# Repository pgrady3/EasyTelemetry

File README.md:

# EasyTelemetry

A simple telemetry board designed to measure many useful things on an Eco-Marathon car. This board will log quantities to an SD card for later analysis, in addition to providing useful information to the driver on an LCD. This design is hopefully easy to extend.

## Features
* 15v-60v operation
* Based on Teensy 3.2 microcontroller
* Uses INA226 for measuring voltage and low-side current
* Measures vehicle speed using hall gear-tooth sensor
* Measures vehicle position using cheap Chinese Ublox NEO-6M GPS modules
* Integrates instataneous power into total energy (joules) consumed
* Compatible with cheap Chinese 20x4 displays with I2C "LCD backpack"
* Uses TE VAL-U-LOK connectors

## Output File

The software creates log files in the following format

```
39.542 2.804 110.87 5.53 294087.16 5380.27 1407101 4.6546335 114.4687347
39.511 3.111 122.93 5.51 294099.44 5380.78 1407201 4.6546288 114.4687347
39.437 3.854 151.98 5.49 294114.66 5381.30 1407301 4.6546235 114.4687347
39.437 3.854 151.98 5.48 294129.84 5381.82 1407401 4.6546183 114.4687347
39.092 7.068 276.28 5.48 294157.47 5382.34 1407501 4.6546135 114.4687347
39.020 7.721 301.29 5.49 294187.59 5382.85 1407601 4.6546082 114.4687347
```

corresponding to
```
voltage(V) current(A) power(w) velocity(m/s) energy(J) distance(m) elapsed time(ms) latitude(DD.dddd) longitude(DD.dddd)
```

## Schematic

## Board

## Software Used

* PCB layout: [Eagle](https://www.autodesk.com/products/eagle/free-download)
* Compiler: [Arduino](https://www.arduino.cc/) with [PJRC Teensyduino add-on](https://www.pjrc.com/teensy/td_download.html)

## Assembly

This respository includes Gerber files which can be directly submitted to PCB manufacturers. We recommend Chinese manufacturers such as [AllPCB](https://www.allpcb.com/) or [JLCPCB](https://jlcpcb.com/). The repository also includes a Bill of Materials (BOM) with Digikey part numbers to order from.

Assembly is straightforward. However, it is recommended to cut the VIN-VUSB trace on the [underside of the Teensy](https://www.pjrc.com/teensy/card7b_rev1.pdf). Cutting the trace means that the Teensy can no longer be powered over USB. This is a safety procaution to prevent the controller feeding power backwards into your computer's USB port. 

## Contact Us

This controller was designed by Patrick Grady from Duke Electric Vehicles. If you need help or clarification, please [send us a message on our website.](http://www.duke-ev.org/dev-contact-us)

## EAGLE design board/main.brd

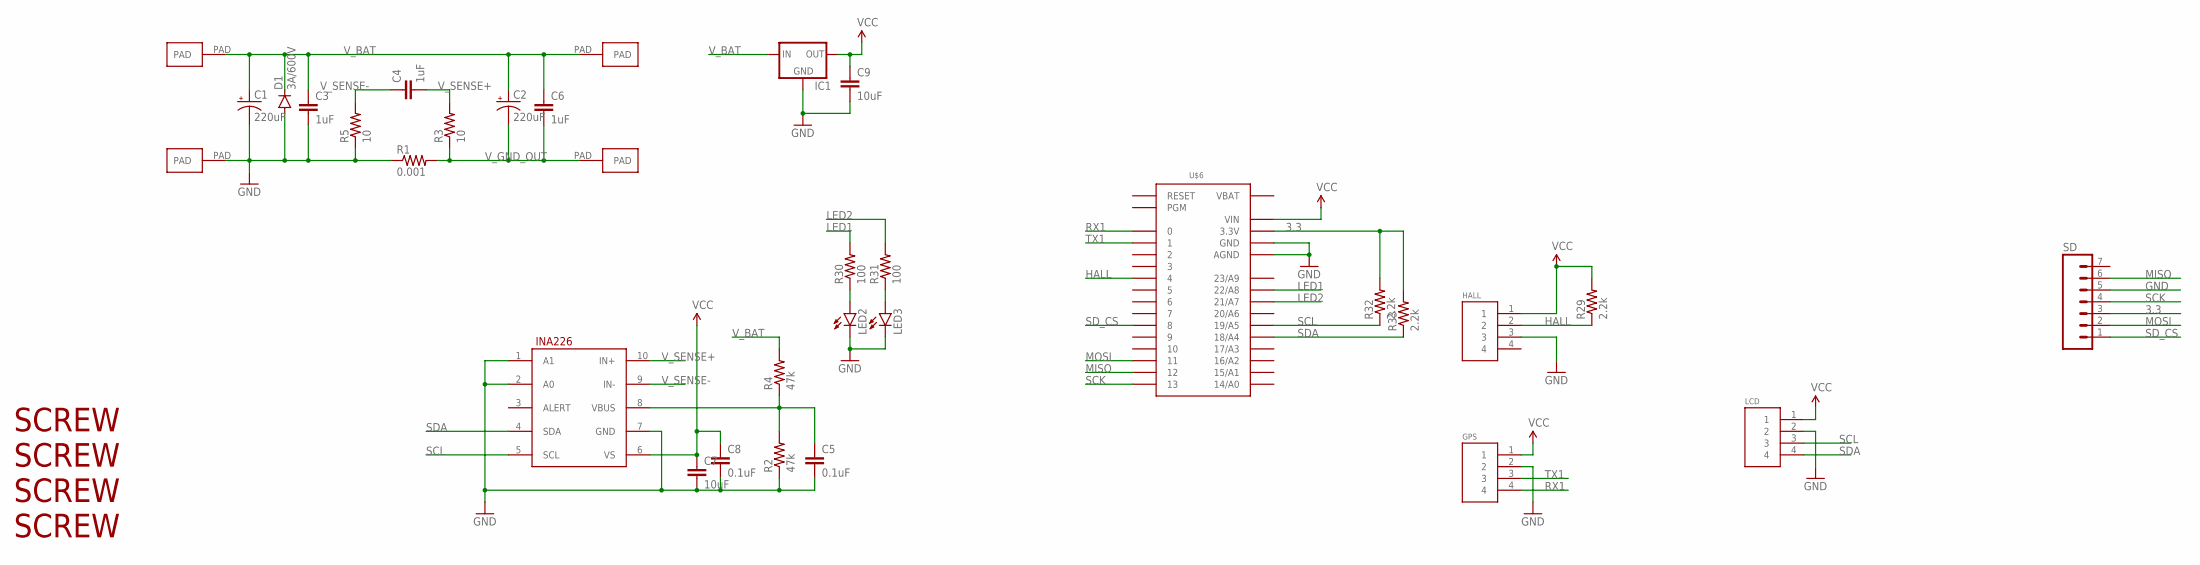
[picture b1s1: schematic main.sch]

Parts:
C1, C2: 220uF; CPOL-RADIAL-1000UF-25V
C3, C4, C6: 1uF; 1206
C5, C8: 0.1uF; 0603-CAP
C7, C9: 10uF; 0805
D1: 3A/600V; SMC
GPS: GPS; 4PINVALULOK
HALL: HEADER4VALULOK; 4PINVALULOK
IC1: V_REG_78XXSINK; TO220-IGO
LCD: GPS; 4PINVALULOK
LED2, LED3: LED1206; LED-1206
R1: 0.001; R2512
R2, R4: 47k; 0603-RES
R3, R5: 10; 0603-RES
R29, R32, R33: 2.2k; 0603-RES
R30, R31: 100; 0603-RES
SD: M07; 1X07
U$1: INA226; PSOP-10
U$2, U$3, U$4, U$5: PAD
U$6: TEENSY_3.0_BASIC
U$13, U$14, U$15, U$16: SCREW; M3HOLE

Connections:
3.3: R32.2, R33.2, SD.3, U$6.3.3V, U$6.3.3V1 (3.3V)
GND: C1.-, C3.2, C5.2, C7.2, C8.2, C9.2, D1.A, GPS.2, HALL.3, IC1.GND, LCD.2, LED2.C, LED3.C, R1.1, R2.1, R5.1, SD.5, U$1.1 (A1), U$1.2 (A0), U$1.7 (GND), U$3.PAD, U$6.AGND, U$6.GND, U$6.GND1 (GND)
HALL: HALL.2, R29.1, U$6.4
LED1: R30.2, U$6.22/A8
LED2: R31.2, U$6.21/A7
MISO: SD.6, U$6.12
MOSI: SD.2, U$6.11
unnamed: C5.1, R2.2, R4.1, U$1.8 (VBUS)
unnamed: LED2.A, R30.1
unnamed: LED3.A, R31.1
RX1: GPS.4, U$6.0
SCK: SD.4, U$6.13
SCL: LCD.3, R32.1, U$1.5 (SCL), U$6.19/A5
SDA: LCD.4, R33.1, U$1.4 (SDA), U$6.18/A4
SD_CS: SD.1, U$6.8
TX1: GPS.3, U$6.1
VBAT: U$6.VBAT
VCC: C7.1, C8.1, C9.1, GPS.1, HALL.1, IC1.OUT, LCD.1, R29.2, U$1.6 (VS), U$6.VIN
V_BAT: C1.+, C2.+, C3.1, C6.1, D1.C, IC1.IN, R4.2, U$2.PAD, U$4.PAD
V_GND_OUT: C2.-, C6.2, R1.2, R3.1, U$5.PAD
V_SENSE+: C4.2, R3.2, U$1.10 (IN+)
V_SENSE-: C4.1, R5.2, U$1.9 (IN-)

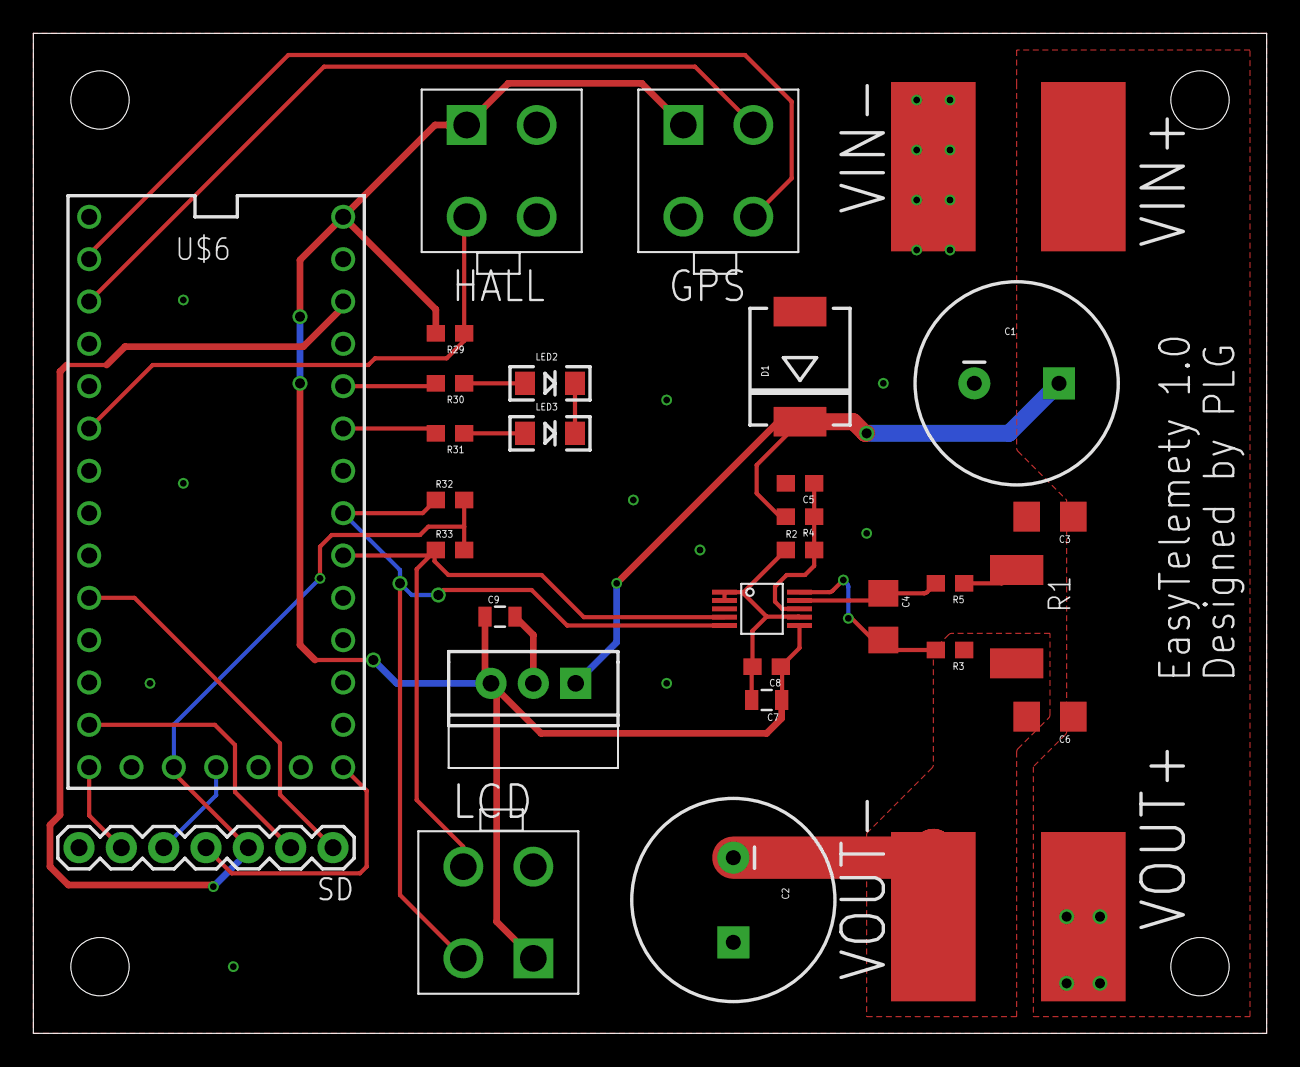
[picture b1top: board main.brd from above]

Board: 2 copper layers, 74.0 x 60.0 mm, 37 parts (0 on the bottom side), 21 nets.

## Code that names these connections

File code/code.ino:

#include <i2c_t3.h>
#include <SD.h>
#include "Adafruit_GPS.h"
#include "LiquidCrystal_I2C.h"
#include "INA.h"

#define LED1 21
#define LED2 22

#define HALL 4
#define SD_CS 8

#define WHEEL_CIRC 1.552
#define WHEEL_TICKS 9
#define TICK_DIST (WHEEL_CIRC / WHEEL_TICKS)

#define TARGET_CURRENT 5

volatile uint32_t tickTimes[WHEEL_TICKS];
volatile uint32_t tickPos;

volatile uint32_t loopTime = 0;
volatile uint32_t lastHallPulse = 0;
volatile uint32_t lastInaMeasurement = 0;
volatile uint32_t countIntervals = 0;
volatile int32_t avgdT = 1000000;
volatile uint32_t distTicks = 0;

double energyUsed = 0.0;
double distance = 0.0;
double currentSpeed = 0.0;
double currentRPM = 0.0;
double InaVoltage = 0.0;
double InaCurrent = 0.0;
double InaPower = 0;
double batteryVoltage = 0.0;
double effScore = 0;

File myFile;
Adafruit_GPS GPS(&Serial1);
LiquidCrystal_I2C lcd(0x27, 20, 4);

void setup() {
  Wire.begin(I2C_MASTER, 0x00, I2C_PINS_18_19, I2C_PULLUP_EXT, 400000);
  INAinit();

  Serial.begin(115200);
  SD.begin(SD_CS);
  lcd.begin();
  lcd.backlight();
  lcd.print("Hello, world!");

  pinMode(LED1, OUTPUT);
  pinMode(LED2, OUTPUT);
  digitalWrite(LED1, HIGH);
  digitalWrite(LED2, HIGH);

  pinMode(HALL, INPUT_PULLUP);
  attachInterrupt(HALL, countHallPulse, FALLING);

  myFile = SD.open("data.txt", FILE_WRITE);
  
  GPSInit();
}

void loop() {  
  GPSPoll();//must be called rapidly
  
  uint32_t curTime = millis();
  if(curTime < loopTime + 100)//if less than 100ms, start over
    return;

  digitalWrite(LED2, !digitalRead(LED2));
  loopTime = curTime;
  
  updateINA();
  updateSpeed();

  writeToBtSd();
  /*char b = GPS.read();
  if(b)
    Serial.print(b);*/
}

void updateINA()
{
  InaVoltage = INAvoltage();
  InaCurrent = INAcurrent();
  InaPower = InaVoltage * InaCurrent;
  
  double currentInaTime = millis();
  energyUsed += InaPower * (currentInaTime - lastInaMeasurement) / 1000;
  lastInaMeasurement = currentInaTime;

  effScore = distance / energyUsed * 3600;
}

void updateSpeed()
{
  currentSpeed = 1000000.0 / avgdT * WHEEL_CIRC; 
  if(micros() - lastHallPulse > 2000000)//if nothing for more than 2 seconds, set speed to zero
    currentSpeed = 0;
  
  distance = distTicks * TICK_DIST;
}

void countHallPulse() {
  uint32_t current = micros();

  uint32_t prevTime = tickTimes[tickPos];// time 1 rev ago. fixed 7/5/2018 :(

  tickTimes[tickPos++] = current;
  tickPos %= WHEEL_TICKS;

  avgdT = current - prevTime;

  distTicks++;
  
  lastHallPulse = current;

  digitalWrite(LED1, (distTicks) & 1);
}

const unsigned char UBLOX_INIT[] = {
  0xB5, 0x62, 0x06, 0x08, 0x06, 0x00, 0x64, 0x00, 0x01, 0x00, 0x01, 0x00, 0x7A, 0x12,//(10Hz)
  0xB5, 0x62, 0x06, 0x01, 0x08, 0x00, 0xF0, 0x01, 0x00, 0x00, 0x00, 0x00, 0x00, 0x01, 0x01, 0x2B, // GxGLL off
  0xB5, 0x62, 0x06, 0x01, 0x08, 0x00, 0xF0, 0x03, 0x00, 0x00, 0x00, 0x00, 0x00, 0x01, 0x03, 0x39, // GxGSV off
  0xB5, 0x62, 0x06, 0x01, 0x08, 0x00, 0xF0, 0x05, 0x00, 0x00, 0x00, 0x00, 0x00, 0x01, 0x05, 0x47, // GxVTG off
  0xB5,0x62,0x06,0x01,0x08,0x00,0xF0,0x00,0x00,0x00,0x00,0x00,0x00,0x01,0x00,0x24, // GxGGA off
  0xB5,0x62,0x06,0x01,0x08,0x00,0xF0,0x02,0x00,0x00,0x00,0x00,0x00,0x01,0x02,0x32, // GxGSA off
  //0xb5, 0x62, 0x06, 0x00, 0x14, 0x00, 0x01, 0x00, 0x00, 0x00, 0xd0, 0x08, 0x00, 0x00, 0x00, 0xc2, 0x01, 0x00, 0x07, 0x00, 0x07, 0x00, 0x00, 0x00, 0x00, 0x00, 0xc4, 0x96, 0xb5, 0x62, 0x06, 0x00, 0x01, //baud rate 115200
  0xB5,0x62,0x06,0x00,0x14,0x00,0x01,0x00,0x00,0x00,0xD0,0x08,0x00,0x00,0x00,0xE1,0x00,0x00,0x07,0x00,0x03,0x00,0x00,0x00,0x00,0x00,0xDE,0xC9,//baud rate 57600
};

void GPSInit()
{
  GPS.begin(9600);
  for (uint32_t i = 0; i < sizeof(UBLOX_INIT); i++) {
    Serial1.write(UBLOX_INIT[i]);
  }
  
  delay(50);
  Serial1.end();
  
  delay(50);
  GPS.begin(57600);
}

void GPSPoll()
{
  while(GPS.read());
  
  if (GPS.newNMEAreceived())
    GPS.parse(GPS.lastNMEA());
}

void writeToBtSd() {
  String outputStr = String(InaVoltage, 3) + " " + String(InaCurrent, 3) + " " + String(InaPower) + " "+ String(currentSpeed) + " " +
                     String(energyUsed) + " " + String(distance) + " " + String(millis()) + " " + String(GPS.latitudeDegrees, 7) + 
                     " " + String(GPS.longitudeDegrees, 7);
  
  Serial.println(outputStr);//usb 
  //Serial.println(GPS.milliseconds); 
  GPSPoll();//super hacky bc short GPS buffer
  
  myFile.println(outputStr);
  myFile.flush();//need this to make sure we actually write to card and don't buffer

  GPSPoll();//super hacky bc short GPS buffer

  lcd.clear();
  LCDWriteFloat(0, 0, InaVoltage, " V");
  LCDWriteFloat(0, 1, InaCurrent, " A");  
  LCDWriteInt(0, 3, GPS.milliseconds, " ms");

  LCDWriteFloat(10, 0, currentSpeed * 3.6, " km/h");
  LCDWriteFloat(10, 1, InaPower, " W");
  LCDWriteFloat(8, 3, effScore, " km/kWh");
}


void LCDWriteFloat(uint8_t x, uint8_t y, float data, const char* s2)
{
  lcd.setCursor(x, y);
  lcd.print(data);
  lcd.print(s2);
  GPSPoll();
}

void LCDWriteInt(uint8_t x, uint8_t y, uint32_t data, const char* s2)
{
  lcd.setCursor(x, y);
  lcd.print(data);
  lcd.print(s2);
  GPSPoll();
}

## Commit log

2020-08-06 Updated documentation
2020-08-06 Improved readme

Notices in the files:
parts and their libraries:
SparkFun-Capacitors: Licensing: Creative Commons ShareAlike 4.0 International - https://creativecommons.org/licenses/by-sa/4.0
